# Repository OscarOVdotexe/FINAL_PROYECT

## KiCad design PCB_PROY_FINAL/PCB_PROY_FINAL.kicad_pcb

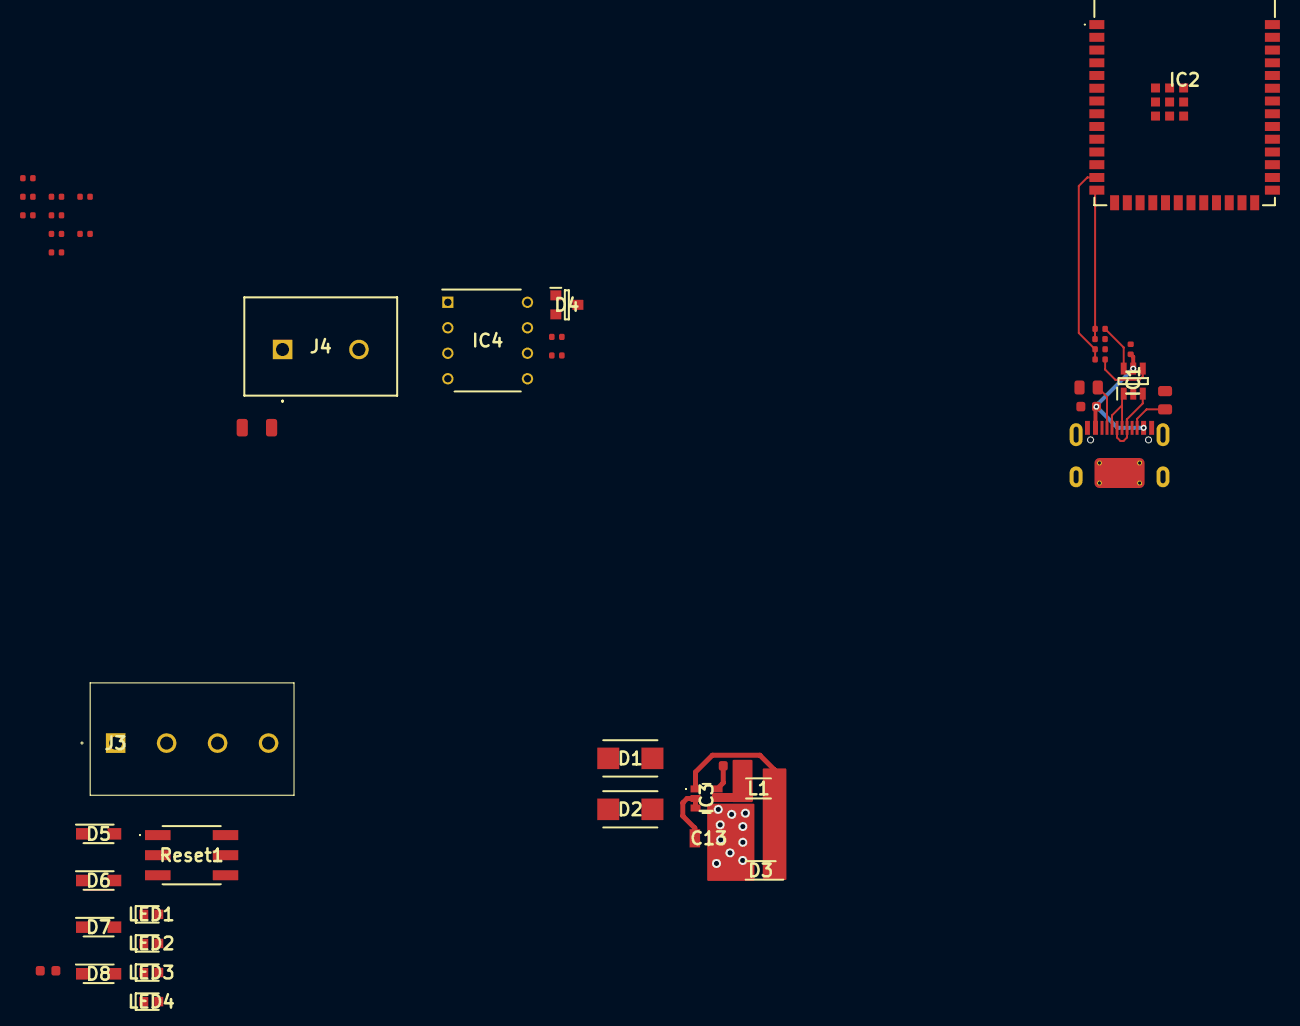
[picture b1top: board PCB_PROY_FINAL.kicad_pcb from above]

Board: 2 copper layers, 46 parts (0 on the bottom side), 32 nets.

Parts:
C1, C10: 22uF; C_0603
C2, C3, C7, C9: 100nF; C_0402
C4, C5: 1nF; C_0402
C11: 100nF; C_0603
C12, C14: 22uF; C_1206
C13: 10uF; CAPC3216X180N
C15, C16: 1uF; C_0402
D1, D2: SS210-E3_52T; DIONM5436X244N
D3, D5, D6, D7, D8: SMF3.3; SOD3718X108N
D4: SM712; SOT95P240X115-3N
IC1: USBLC6-2SC6; SOT95P280X145-6N
IC2: ESP32-S3-WROOM-1-N16; ESP32S3WROOM1N16
IC3: AP63203WU-7; AP63203WU7
IC4: SN75176BP; DIP794W53P254L959H508Q8N
J1: Connector, USB-TYPE-C-16P; TYPE-C-SMD_HX-TYPE-C-16PIN
J3: 1712805
J4: 1717729
L1: NLV25T-3R9J-PF; INDM2520X190N
LED1, LED2, LED3, LED4: KT-0603R; LEDC1608X70N
R1: 10kΩ; R_0402
R2: 120Ω; R_1206
R3, R4, R5, R11: 220Ω; R_0402
R6, R8: 33Ω; R_0402
R7: 4.7kΩ; R_0402
R9, R10: 5.1kΩ; R_0805
Reset1: XKB5858-W-TP; XKB5858WTP

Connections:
/Alimentacion/V3.3: C1.1, C2.1, C3.1, C12.1, C14.1, D3.1 (K), IC2.2 (3V3), IC2.27 (IO0), IC3.1 (FB), IC4.8 (VCC), L1.2, R1.1, R7.1
/Alimentacion/VUSB: C9.2, C10.1, D2.2 (A), IC1.5 (VBUS), J1.A9B4 (VBUS), J1.B9A4 (VBUS)
/ESPS3/RTS: IC2.18 (IO10), IC4.2 (~RE), IC4.3 (DE)
/ESPS3/RX: IC2.12 (IO8), IC4.1 (R)
/ESPS3/TX: IC2.17 (IO9), IC4.4 (D)
/RS485_CONEX/A: C4.1, D4.2 (CATHODE_2), IC4.6 (A), J4.1, R2.1
/RS485_CONEX/B: C5.1, D4.1 (CATHODE_1), IC4.7 (B), J4.2, R2.2
ADC2_CH0: IC2.19 (IO11), J3.4
ADC_CH0: IC2.39 (IO1), J3.1
ADC_CH1: IC2.38 (IO2), J3.2
ADC_CH3: IC2.15 (IO3), J3.3
D+: C15.1, IC2.14 (IO20), R6.1
D-: C16.1, IC2.13 (IO19), R8.1
EN: C7.2, IC2.3 (EN), R1.2, Reset1.1 (NO_1)
GND: C1.2, C2.2, C3.2, C4.2, C5.2, C7.1, C9.1, C10.2, C12.2, C13.1, C14.2, C15.2, C16.2, D3.2 (A), D4.3 (COMMON_CATHODE), D5.2 (A), D6.2 (A), D7.2 (A), D8.2 (A), IC1.2 (GND), IC2.1 (GND_1), IC2.40 (GND_2), IC2.41 (GND_3), IC2.42 (GND_4), IC2.43 (GND_5), IC2.44 (GND_6), IC2.45 (GND_7), IC2.46 (GND_8), IC2.47 (GND_9), IC2.48 (GND_10), IC2.49 (GND_11), IC3.4 (GND), IC4.5 (GND), J1.A12B1 (GND), J1.B12A1 (GND), J1.S1 (SHIELD), LED1.1 (K), LED2.1 (K), LED3.1 (K), LED4.1 (K), R7.2, R9.2, R10.2, Reset1.2 (COM_1)
LED1: D5.1 (K), IC2.4 (IO4), R3.1
LED2: D6.1 (K), IC2.5 (IO5), R4.1
LED3: D7.1 (K), IC2.6 (IO6), R5.1
LED4: D8.1 (K), IC2.7 (IO7), R11.1
unnamed: C13.2, D1.1 (K), D2.1 (K), IC3.2 (EN), IC3.3 (VIN)
unnamed: IC1.1 (I/O1_1), J1.A7 (D-), J1.B7 (D-)
unnamed: IC1.6 (I/O1_2), R6.2
unnamed: IC1.3 (I/O2_1), J1.A6 (D+), J1.B6 (D+)
unnamed: IC1.4 (I/O2_2), R8.2
unnamed: C11.1, IC3.6 (BST)
unnamed: C11.2, IC3.5 (SW), L1.1
unnamed: J1.A5 (CC1), R9.1
unnamed: J1.B5 (CC2), R10.1
unnamed: LED1.2 (A), R3.2
unnamed: LED2.2 (A), R4.2
unnamed: LED3.2 (A), R5.2
unnamed: LED4.2 (A), R11.2

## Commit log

2025-03-15 Last update pcb
2025-03-15 new changes
